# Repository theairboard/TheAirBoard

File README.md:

[The AirBoard: sketch everyware](http://www.theairboard.cc)
=============================================
[order yours now](http://sales.theairboard.cc)

Summary
-------
The AirBoard is a wireless, modular and ultra low-power Arduino prototyping platform for the Internet of Things, designed to explore, hack and deploy your killer idea in the field.

<b>Note:</b> The AirBoard is CE certified and comes with a UL1642, CB/IEC62133, UN38.3 fully certified built-in battery.

<b>Note:</b> The AirBoard has been designed to be wirelessly reprogrammable. The microUSB connector is used for battery charging only. To upload a new program, you will need additional wireless shields such as XBee or BLE and their associated USB dongle, or an external serial connection over FTDI.

Features
-----------
<b>Go wireless</b><br>
Explore the hotest wireless technologies today: with its popular Bee form factor, the AirBoard features a socket for XBee, Bluetooth, BLE and WiFi wireless shields, as well as the recent GSM/GPRS, SIGFOX and LoRa WAN long range IoT modules. Simply swap the radio for instant communication and WPAN Over-The-Air Programming.<br>
<br>
<b>Iterate quickly</b><br>
The AirBoard was designed with productivity in mind. Design and iterate quickly with the built-in open solderless breadboard. Only Arduino’s most popular I/Os are exposed, in order to lower the cognitive barrier and encourage the highest experiment turnover. Snap in hundreds of sensors and experiment a whole library of interactions in just seconds.<br>
<br>
<b>Deploy your device in the field</b><br>
Beyond the Internet of Things, ubiquitous devices require efficient Power and Data Management strategies to become truly autonomous.<br>
<br>
<b>Ultra Power Efficient</b><br>
Forget about your sensors with the built-in battery and Power Management System. The AirBoard is designed for ultra low-power applications, yet capable to drive long range wireless shields. It offers an ultra-low power sleep mode with switchable radio for most efficient communication strategy.<br>
<br>
<b>Your first sketch in seconds</b><br>
Start programming straight from the box with this superb web IDE by codebender. All required libraries and quick start source codes have been installed already. And with the pre-loaded Arduino Fio bootloader, you can also use the Arduino IDE. So why don’t you wait and start sketching now!<br>
<br>
<b>Make your own App</b><br>
It’s no longer needed to be an expert in programming to build pretty AND functional Graphical User Interfaces. Have fun interacting with your tangible hardware right away! Just drag and drop a whole library of widgets to build your own mobile app. remotexy and Blynk work seamlessly with the AirBoard and are great examples of bringing rapid prototyping to everyone.<br>

Specification
-------------

<b>Size and Weight</b>

    41x25x9mm
    Weight, including battery: 10g

<b>Native Arduino Processor</b>

    Arduino compatible
    ATmega328P processor @ 8MHz
    Pre-loaded Arduino Fio bootloader
    Arduino IDE support
    codebender web IDE support

<b>Open solderless breadboard and socket headers</b>

    7x GPIO, I2C, SPI, 2x 10-bit ADC, 3x PWM
    5VUSB/500mA, 3.3V/200mA power outputs
    Up to 18x GPIOs, 6x 10-bit analog inputs or 6x PWMs

<b>Bright RGB LED</b>

    RGB LED, up to 2240mcd, 120° viewing angle

<b>Wireless</b>

    « Bee » socket form factor
    Wireless support: XBee, Bluetooth 2.1,  Bluetooth Low Energy 4.0, WiFi,GSM/GPRS, SIGFOX, LoRa WAN
    2-channel Over-The-Air Programming (OTAP)
    5-second programming via XBee, Bluetooth, WiFi

<b>Ultra Low Power Management System</b>

    155mAh rechargeable lithium-ion battery
    1A switchable RF LDO
    330nA system deep sleep
    Autonomy in sleep mode: 2-3 years
    Autonomy in communication: 6 months (XBee 1 data/minute)

<b>Built-in battery charger</b>

    1-cell Li-ion USB charger
    Battery Over Current, Charge & Discharge protect
    Battery level indicator, charge status, USB voltage monitor
    Charge time: 1.5 hours

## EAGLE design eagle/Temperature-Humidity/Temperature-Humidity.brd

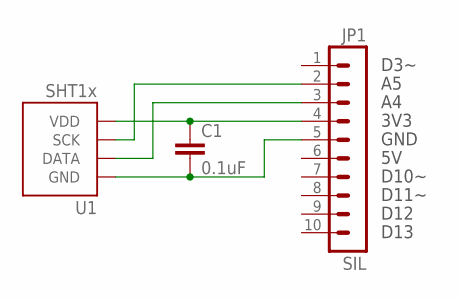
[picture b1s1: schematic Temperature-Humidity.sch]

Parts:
C1: 0.1uF; 0603-CAP
JP1: SIL; SIL-1X10
U1: SHT1x; SHT1X

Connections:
GND: C1.2, JP1.5, U1.1 (GND)
unnamed: JP1.2, U1.3 (SCK)
unnamed: JP1.3, U1.2 (DATA)
VDD: C1.1, JP1.4, U1.4 (VDD)

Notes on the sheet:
D3~
3V3
GND
D10~
D11~
D12
D13

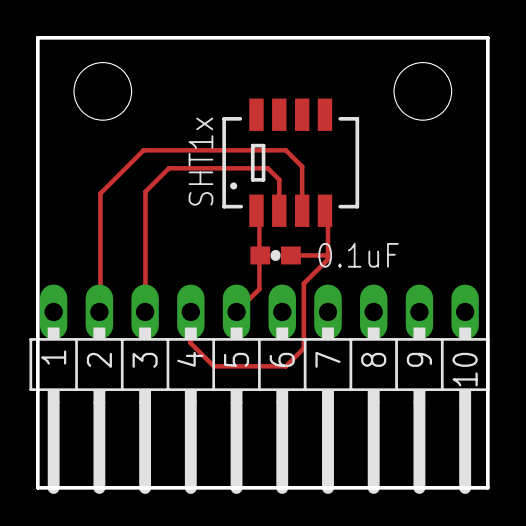
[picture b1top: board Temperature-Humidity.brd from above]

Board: 2 copper layers, 25.0 x 25.0 mm, 5 parts (0 on the bottom side), 4 nets.

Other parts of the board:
FRAME1: SCH_FRAME; BOARD_FRAME
U$2: LAYOUT25X25

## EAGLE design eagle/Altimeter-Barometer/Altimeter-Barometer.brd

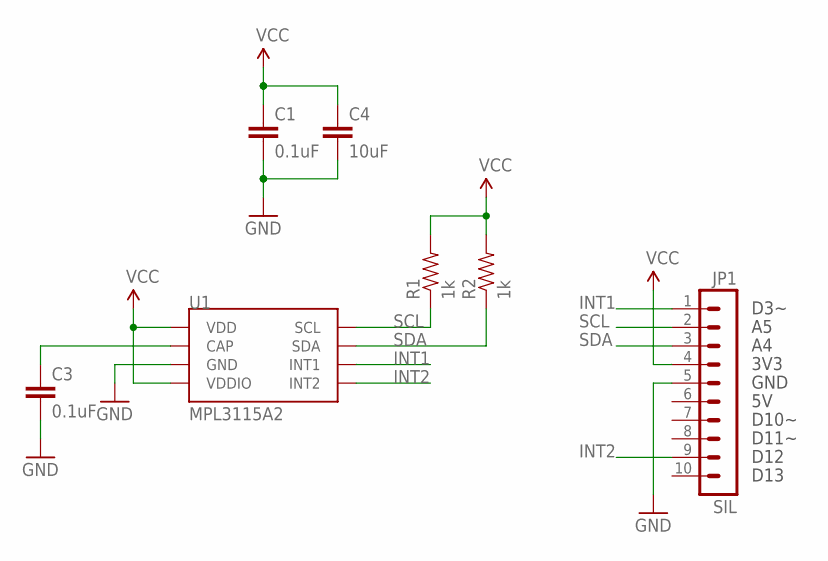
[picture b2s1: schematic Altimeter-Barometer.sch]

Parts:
C1, C3: 0.1uF; 0603-CAP
C4: 10uF; 0805
JP1: SIL; SIL-1X10
R1, R2: 1k; 0603-RES
U1: MPL3115A2; LGA8

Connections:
CAP: C3.1, U1.2 (CAP)
GND: C1.2, C3.2, C4.2, JP1.5, U1.3 (GND)
INT1: JP1.1, U1.6 (INT1)
INT2: JP1.9, U1.5 (INT2)
SCL: JP1.2, R1.1, U1.8 (SCL)
SDA: JP1.3, R2.1, U1.7 (SDA)
VCC: C1.1, C4.1, JP1.4, R1.2, R2.2, U1.1 (VDD), U1.4 (VDDIO)

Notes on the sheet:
D3~
3V3
GND
D10~
D11~
D12
D13

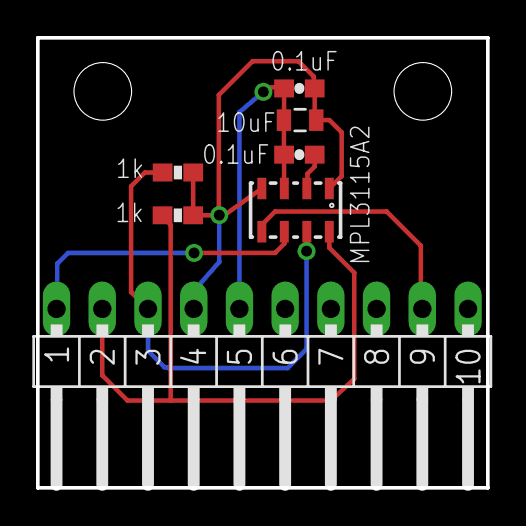
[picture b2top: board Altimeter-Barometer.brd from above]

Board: 2 copper layers, 25.0 x 25.0 mm, 9 parts (0 on the bottom side), 7 nets.

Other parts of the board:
FRAME1: SCH_FRAME; BOARD_FRAME
U$2: LAYOUT25X25

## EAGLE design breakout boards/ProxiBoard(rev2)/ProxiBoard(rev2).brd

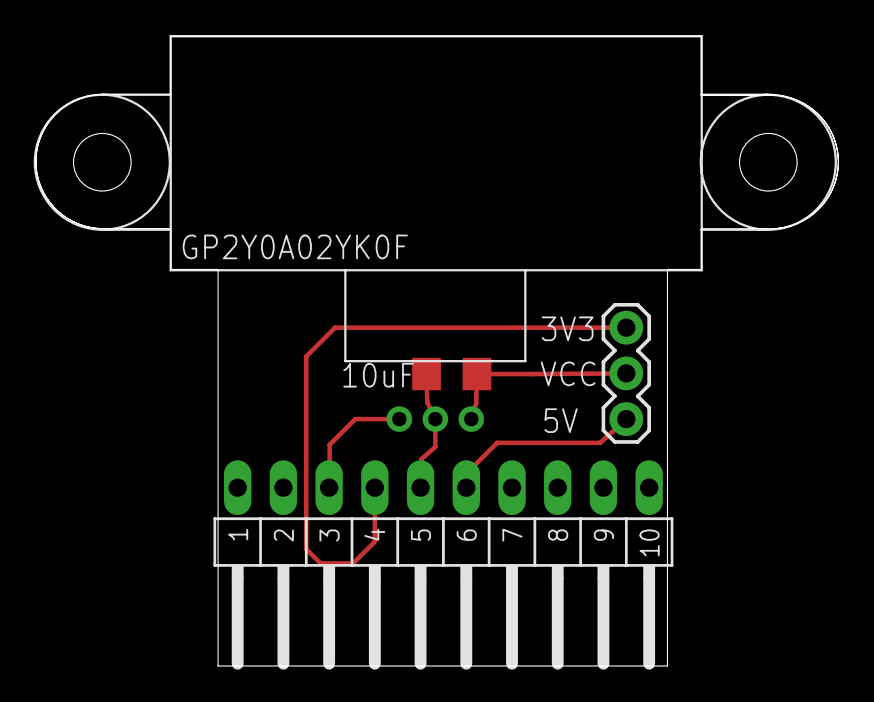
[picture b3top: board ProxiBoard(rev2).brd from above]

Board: 2 copper layers, 44.6 x 35.0 mm, 5 parts (0 on the bottom side), 5 nets.

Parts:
C1: 10uF; 1206
FRAME1: SCH_FRAME; BOARD_FRAME
JP1: SIL; SIL10-2.54MM
JP2: 1X03
U1: GP2Y0A02YK0F

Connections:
3V3: JP1.4, JP2.3
5V: JP1.6, JP2.1
A4: JP1.3, U1.1
unnamed: C1.1, JP2.2, U1.3
unnamed: C1.2, JP1.5, U1.2

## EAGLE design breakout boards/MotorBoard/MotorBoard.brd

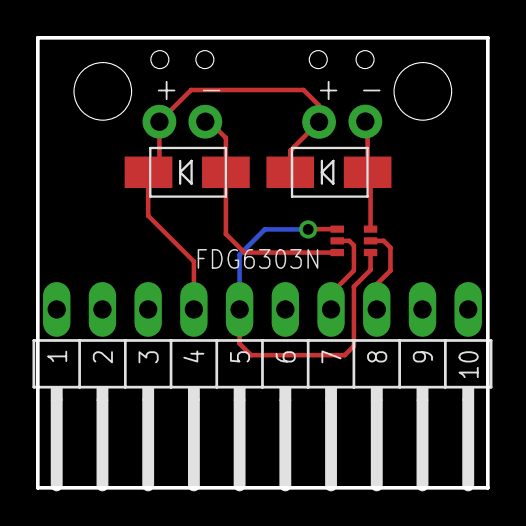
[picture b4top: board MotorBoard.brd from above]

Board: 2 copper layers, 25.0 x 25.0 mm, 10 parts (0 on the bottom side), 6 nets.

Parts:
D1, D2: S1M; DO-214AC
FRAME1: SCH_FRAME; BOARD_FRAME
JP1: SIL; SIL10-2.54MM
JP2, JP3, JP4, JP5: M01SMDNS; 1X01NS
Q1: FDG6303N; SC70-6
U$1: LAYOUT25X25

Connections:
GND: JP1.5, Q1.1, Q1.4
unnamed: JP1.7, Q1.5
unnamed: JP1.8, Q1.2
unnamed: D2.1, JP4.1, Q1.6
unnamed: D1.1, JP2.1, Q1.3
VCC: D1.2, D2.2, JP1.4, JP3.1, JP5.1

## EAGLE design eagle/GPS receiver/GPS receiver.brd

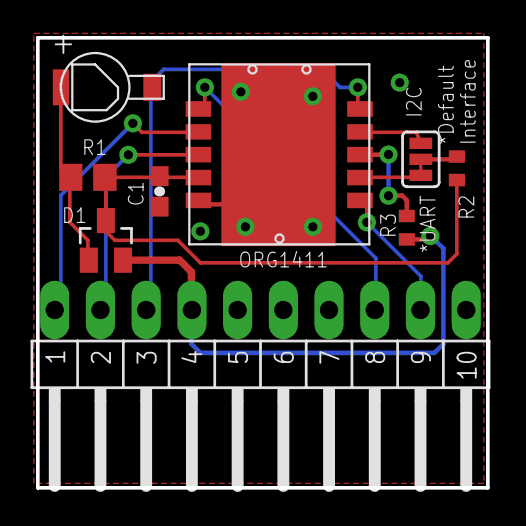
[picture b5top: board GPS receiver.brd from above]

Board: 2 copper layers, 25.0 x 25.0 mm, 11 parts (0 on the bottom side), 12 nets.

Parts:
C1: 0.1uF; 0603-CAP
C2: 0.03F; PAS311-VA6R
D1: SB05W05C; SOT23
FRAME1: SCH_FRAME; BOARD_FRAME
JP1: SIL; SIL10-2.54MM
JP2: JUMPER-3SMD; SJ_3
R1: 56; R0805
R2, R3: 1K; R0402
U2: ORG1411
U$2: LAYOUT25X25WO

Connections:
1PPS: JP1.1, U2.2
+3V3: D1.2, JP1.4, R3.1
GND: C1.2, C2.-, JP1.5, U2.5, U2.GND
I2C: JP2.3, U2.9
unnamed: R3.2, U2.8
unnamed: C2.+, D1.1, R1.1
ONOFF: JP1.8, U2.1
RX: JP1.3, U2.10
SER: JP2.1, JP2.2, R2.1, U2.7
TX: JP1.2, U2.3
VCC: C1.1, D1.3, R1.2, R2.2, U2.4
WUP: JP1.9, U2.6

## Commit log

2014-11-30 The AirBoard library
2014-11-30 Added baud rate parameter to powerDown function
2014-12-06 Proto boards library 0.1
2014-12-13 Added apk, stl and protoboard
2014-12-21 Added GPS receiver
2014-12-30 added Low-Power XBee and WiFi data logger examples
2014-12-30 specified firmware version for WiFi data logger
2015-01-03 - set green led value to minimum to avoid glare - completed firmware version for WiFi data logger
2015-01-24 Added draft schematics
2015-01-25 Added sample apps and code
2015-01-25 Datasheets
2015-01-27 Added RemoteXY sample code and lib
2015-01-29 Added Low-Power data logger, BLE app, OriginGPS
2015-02-02 Added RemoteXY sample sketches
2015-02-03 Added ADXL345 lib
2015-02-07 Updated low-power figure
2015-02-11 Added SigFox logger
2015-02-14 Added DI-O library and sample code
2015-02-16 Added 433MHz transmitter
2015-03-12 Initial Release
2015-03-12 fix directory name
2015-03-26 Design update
    Add backup battery
    Add jumper to select between i2c or UART default interface
2015-03-26 Update
    Add resistor on /RESET input to automatic shutdown the receiver when no
    primary supply
2015-06-30 erase all
2015-06-30 Kickstarter commit
2015-07-27 Update sketchBit
2015-07-27 Update Blink
2015-07-29 Update proximity sensor
2015-08-23 added Color example
2015-08-23 added apt link
2015-08-24 added Bluetooth 2 Color app
2015-08-29 added BrushBot BLE
2015-09-01 updated title
2015-09-08 updated tAB-Direction
2015-10-25 Updated baud rate
2015-11-05 added Android sources
2015-11-08 corrected tAB-Direction.apk url
2015-11-12 corrected Color codes
2015-12-19 added Neopixel, Blynk and LoRaWAN examples
2015-12-24 corrected LoRa comment
2016-01-03 updated breakout boards
2016-03-21 added SigBee logger
2016-04-09 added power-up delay from sleep
2016-04-25 doubled delay in RN42 configuration
2016-06-18 mod powerDown, add getTemp
    - in powerDown function, changed baudrate restoration method upon
    recover from sleep
    - added getTemp function to return internal MCU temperature in °C
2016-06-18 added getTemp function
    added getTemp function to return internal MCU temperature in °C
2017-02-15 added boot delay in SigBee_logger
2017-06-02 updated SigBee_logger
2017-06-14 updated SigBee logger
2017-11-27 re-synch github

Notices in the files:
parts and their libraries:
theairboard: Released under the Creative Commons
theairboard: https://creativecommons.org/licenses/by-sa/4.0
SparkFun-Connectors: Licensing: Creative Commons ShareAlike 4.0 International - https://creativecommons.org/licenses/by-sa/4.0
